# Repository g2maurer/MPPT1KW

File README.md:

# MPPT1KW
 Solar Battery Charger
   1. 4/18/2023 Added PCB files (KiCad).
   2. 10/11/2023 Updated BOM files:
      MPPT_1KW_ESP32_ggmV3.xlsx
      MPPT V3 BOM.pdf
   4. 04/23/2024 Added new enclosure design (new design was done with FreeCAD).
      The dimensions have not changed but the new design incorporates the fan and vent grills.

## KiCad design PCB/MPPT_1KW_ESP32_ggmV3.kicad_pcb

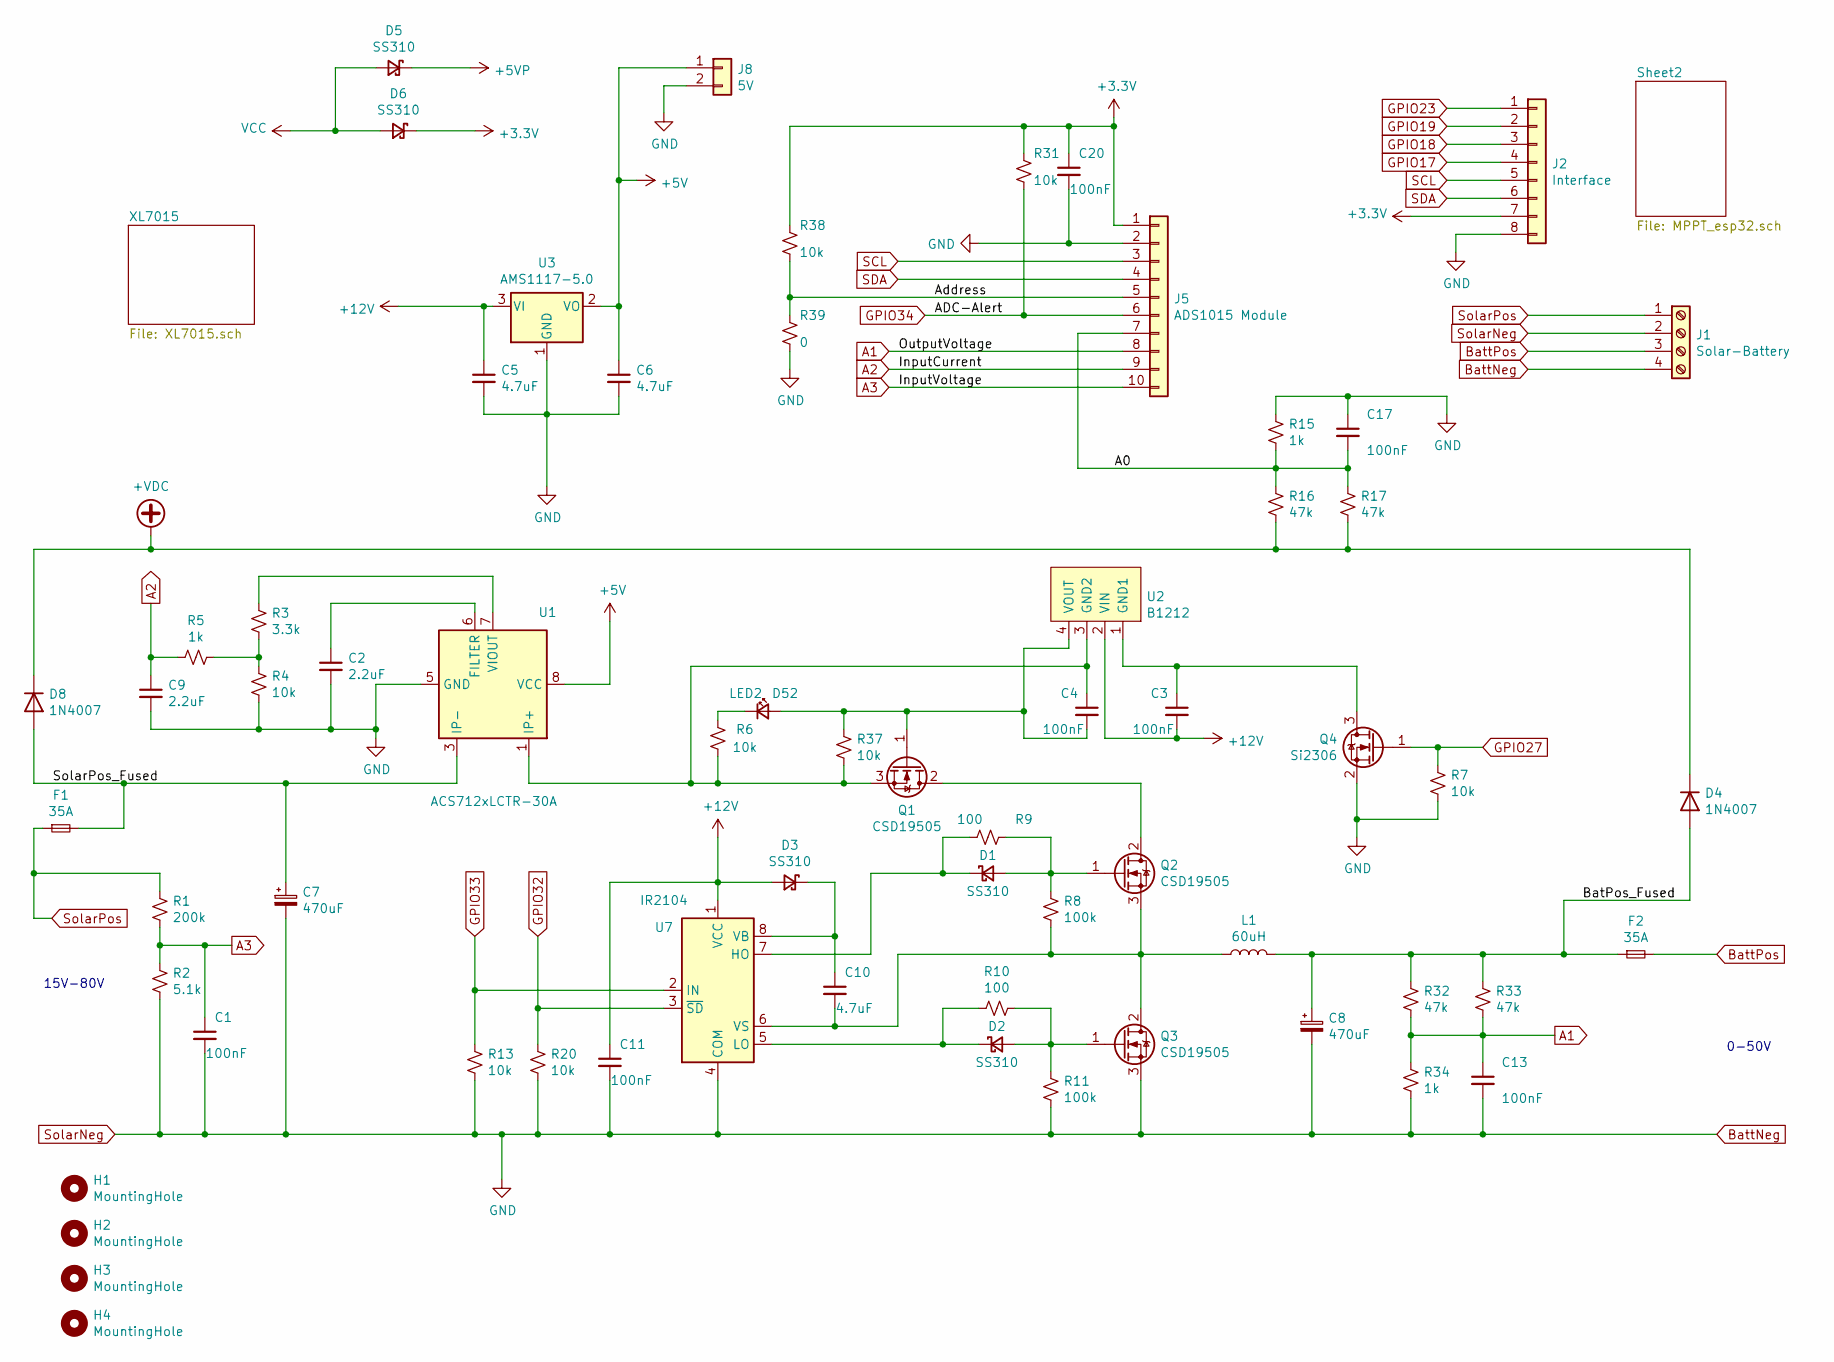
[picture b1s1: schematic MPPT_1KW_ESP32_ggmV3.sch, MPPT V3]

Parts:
C1, C3, C4, C11, C13, C17, C20: 100nF; C_0805_2012Metric_Pad1.18x1.45mm_HandSolder
C2, C9: 2.2uF; C_0805_2012Metric_Pad1.18x1.45mm_HandSolder
C5, C6, C10: 4.7uF; C_1206_3216Metric_Pad1.33x1.80mm_HandSolder
C7, C8: 470uF; CP_Radial_D16.0mm_P7.50mm
D1, D2, D3, D5, D6: SS310; D_2010_5025Metric_Pad1.52x2.65mm_HandSolder
D4, D8: 1N4007; D_2010_5025Metric_Pad1.52x2.65mm_HandSolder
D52: LED2; LED_0805_2012Metric_Pad1.15x1.40mm_HandSolder
F1, F2: 35A; Mini_Blade
H1, H2, H3, H4: MountingHole; MountingHole_2.7mm
J1: Solar-Battery; Conn-Screw-4-term
J2: Interface; JST_XH_B8B-XH-A_1x08_P2.50mm_Vertical
J5: ADS1015 Module; JST_XH_B10B-XH-A_1x10_P2.50mm_Vertical
J8: 5V; JST_XH_B2B-XH-A_1x02_P2.50mm_Vertical
L1: 60uH; L_Toroid_Vertical_L41.9mm_W17.8mm_P12.70mm_Pulse_F
Q1, Q2, Q3: CSD19505; TO-220-3_Vertical
Q4: Si2306; SOT-23
R1: 200k; R_0805_2012Metric_Pad1.20x1.40mm_HandSolder
R2: 5.1k; R_0805_2012Metric_Pad1.20x1.40mm_HandSolder
R3: 3.3k; R_0805_2012Metric_Pad1.20x1.40mm_HandSolder
R4, R6, R7, R13, R20, R31, R37, R38: 10k; R_0805_2012Metric_Pad1.20x1.40mm_HandSolder
R5, R15, R34: 1k; R_0805_2012Metric_Pad1.20x1.40mm_HandSolder
R8, R11: 100k; R_0805_2012Metric_Pad1.20x1.40mm_HandSolder
R9, R10: 100; R_0805_2012Metric_Pad1.20x1.40mm_HandSolder
R16, R17, R32, R33: 47k; R_0805_2012Metric_Pad1.20x1.40mm_HandSolder
R39: 0; R_0805_2012Metric_Pad1.20x1.40mm_HandSolder
U1: ACS712xLCTR-30A; SOIC-8_3.9x4.9mm_P1.27mm
U2: B1212; B1212S
U3: AMS1117-5.0; SOT-223-3_TabPin2
U7: IR2104; SOIC-8_3.9x4.9mm_P1.27mm

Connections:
+3V3: C20.1, D6.1 (K), J2.7, J5.1, R31.1, R38.1; also elsewhere on the board
+5V: C6.1, J8.1, U1.8 (VCC), U3.2 (VO)
+5VP: D5.1 (K); also elsewhere on the board
+12V: C3.2, C5.1, C11.1, D3.2 (A), U2.2 (VIN), U3.3 (VI), U7.1 (VCC); also elsewhere on the board
+VDC: D4.1 (K), D8.1 (K), R16.2, R17.2; also elsewhere on the board
/A0: C17.2, J5.7, R15.2, R16.1, R17.1
/Address: J5.5, R38.2, R39.1
/BatPos_Fused: C8.1, D4.2 (A), F2.1, L1.2, R32.1, R33.1
/SolarPos_Fused: C7.1, D8.2 (A), F1.2, U1.3 (IP-), U1.4 (IP-)
A1: C13.1, J5.8, R32.2, R33.2, R34.1
A2: C9.1, J5.9, R5.2
A3: C1.1, J5.10, R1.2, R2.1
BattNeg: C1.2, C2.2, C5.2, C6.2, C7.2, C8.2, C9.2, C11.2, C13.2, C17.1, C20.2, J1.2, J1.4, J2.8, J5.2, J8.2, Q3.3 (S), Q4.2 (S), R2.2, R4.2, R7.2, R11.2, R13.2, R15.1, R20.2, R34.2, R39.2, U1.5 (GND), U3.1 (GND), U7.4 (COM); also elsewhere on the board
BattPos: F2.2, J1.3
GPIO17: J2.4; also elsewhere on the board
GPIO18: J2.3; also elsewhere on the board
GPIO19: J2.2; also elsewhere on the board
GPIO23: J2.1; also elsewhere on the board
GPIO27: Q4.1 (G), R7.1; also elsewhere on the board
GPIO32: R20.1, U7.3 (~SD); also elsewhere on the board
GPIO33: R13.1, U7.2 (IN); also elsewhere on the board
GPIO34: J5.6, R31.2; also elsewhere on the board
unnamed: C2.1, U1.6 (FILTER)
unnamed: C3.1, Q4.3 (D), U2.1 (GND1)
unnamed: C4.1, Q1.3 (S), R6.1, R37.2, U1.1 (IP+), U1.2 (IP+), U2.3 (GND2)
unnamed: C4.2, D52.2 (A), Q1.1 (G), R37.1, U2.4 (VOUT)
unnamed: C10.1, D3.1 (K), U7.8 (VB)
unnamed: C10.2, L1.1, Q2.3 (S), Q3.2 (D), R8.2, U7.6 (VS)
unnamed: D1.1 (K), R9.2, U7.7 (HO)
unnamed: D1.2 (A), Q2.1 (G), R8.1, R9.1
unnamed: D2.1 (K), R10.2, U7.5 (LO)
unnamed: D2.2 (A), Q3.1 (G), R10.1, R11.1
unnamed: D52.1 (K), R6.2
unnamed: Q1.2 (D), Q2.2 (D)
unnamed: R3.1, U1.7 (VIOUT)
unnamed: R3.2, R4.1, R5.1
SCL: J2.5, J5.3; also elsewhere on the board
SDA: J2.6, J5.4; also elsewhere on the board
SolarPos: F1.1, J1.1, R1.1
VCC: D5.2 (A), D6.2 (A); also elsewhere on the board

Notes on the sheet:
15V-80V
0-50V

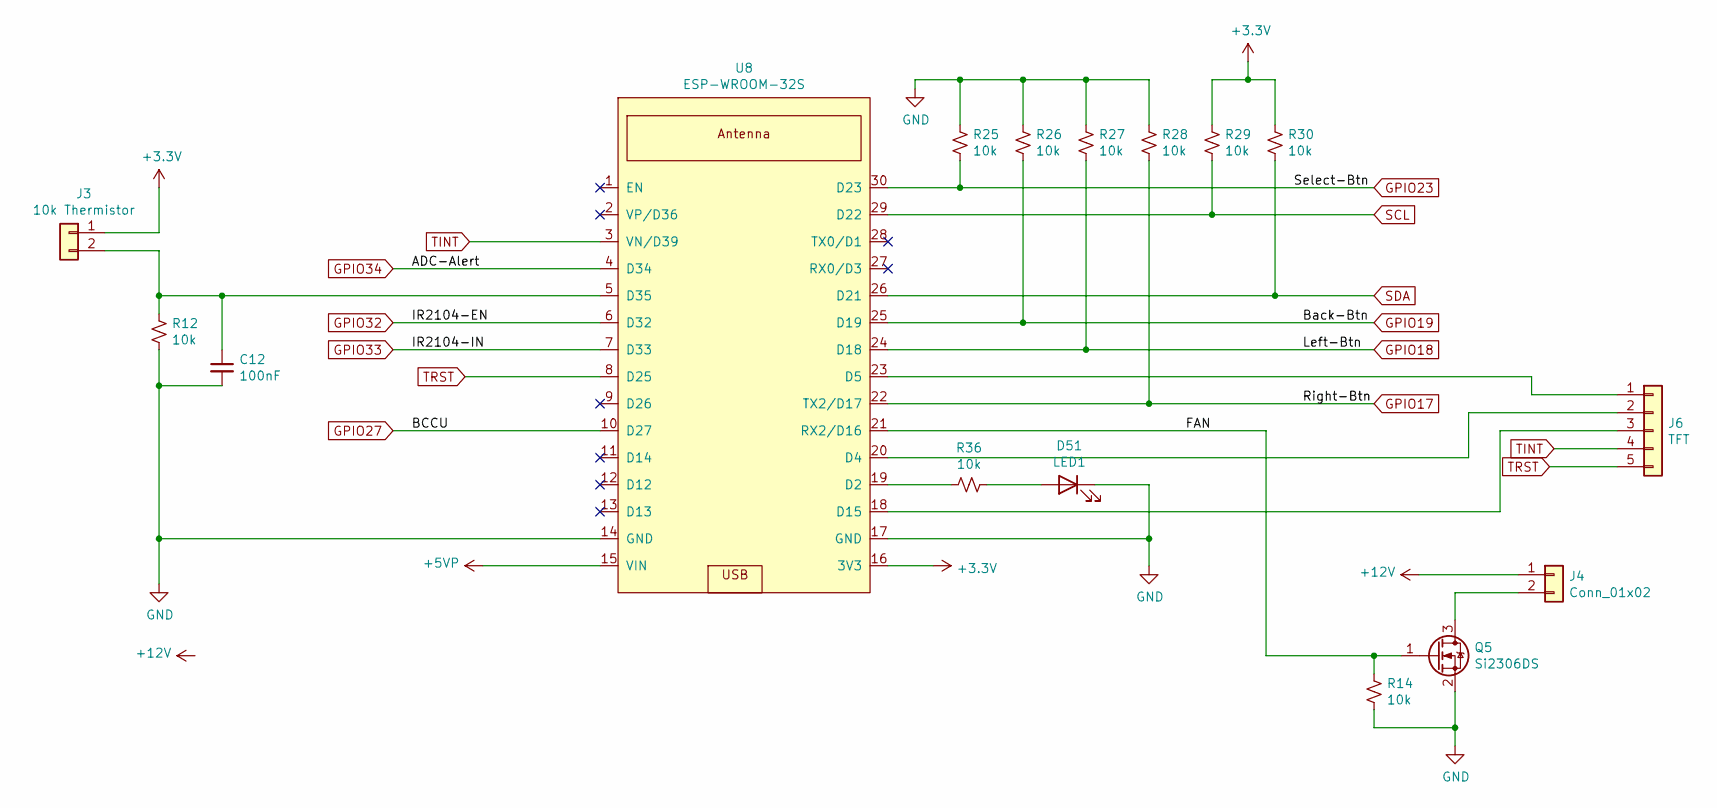
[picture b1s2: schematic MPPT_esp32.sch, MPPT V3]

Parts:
C12: 100nF; C_0805_2012Metric_Pad1.18x1.45mm_HandSolder
D51: LED1; LED_0805_2012Metric_Pad1.15x1.40mm_HandSolder
J3: 10k Thermistor; JST_XH_B2B-XH-A_1x02_P2.50mm_Vertical
J4: Conn_01x02; JST_XH_B2B-XH-A_1x02_P2.50mm_Vertical
J6: TFT; JST_XH_B5B-XH-A_1x05_P2.50mm_Vertical
Q5: Si2306DS; SOT-23
R12, R14, R25, R26, R27, R28, R29, R30, R36: 10k; R_0805_2012Metric_Pad1.20x1.40mm_HandSolder
U8: ESP-WROOM-32S

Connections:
+3V3: J3.1, R29.1, R30.1, U8.16 (3V3); also elsewhere on the board
+5VP: U8.15 (VIN); also elsewhere on the board
+12V: J4.1; also elsewhere on the board
/Sheet2/FAN: Q5.1 (G), R14.1, U8.21 (RX2/D16)
BattNeg: C12.2, D51.1 (K), Q5.2 (S), R12.2, R14.2, R25.1, R26.1, R27.1, R28.1, U8.14 (GND), U8.17 (GND); also elsewhere on the board
GPIO17: R28.2, U8.22 (TX2/D17); also elsewhere on the board
GPIO18: R27.2, U8.24 (D18); also elsewhere on the board
GPIO19: R26.2, U8.25 (D19); also elsewhere on the board
GPIO23: R25.2, U8.30 (D23); also elsewhere on the board
GPIO27: U8.10 (D27); also elsewhere on the board
GPIO32: U8.6 (D32); also elsewhere on the board
GPIO33: U8.7 (D33); also elsewhere on the board
GPIO34: U8.4 (D34); also elsewhere on the board
unnamed: C12.1, J3.2, R12.1, U8.5 (D35)
unnamed: D51.2 (A), R36.1
unnamed: J4.2, Q5.3 (D)
unnamed: J6.1, U8.23 (D5)
unnamed: J6.2, U8.20 (D4)
unnamed: J6.3, U8.18 (D15)
unnamed: R36.2, U8.19 (D2)
SCL: R29.2, U8.29 (D22); also elsewhere on the board
SDA: R30.2, U8.26 (D21); also elsewhere on the board
TINT: J6.4, U8.3 (VN/D39)
TRST: J6.5, U8.8 (D25)

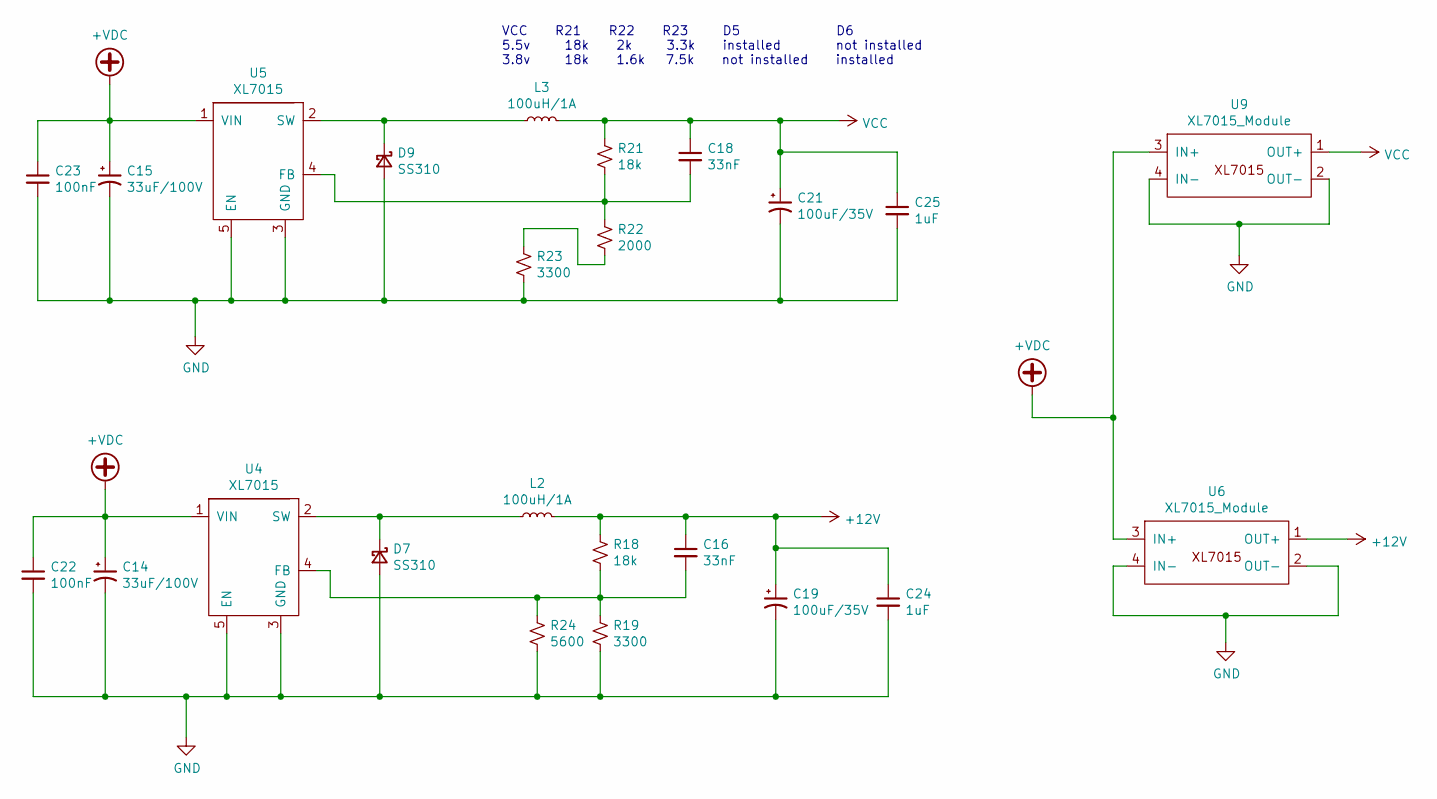
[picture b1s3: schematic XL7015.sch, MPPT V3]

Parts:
C14, C15: 33uF/100V; CP_Radial_D8.0mm_P2.50mm
C16, C18: 33nF; C_0805_2012Metric_Pad1.18x1.45mm_HandSolder
C19, C21: 100uF/35V; CP_Radial_D6.3mm_P2.50mm
C22, C23: 100nF; C_0805_2012Metric_Pad1.18x1.45mm_HandSolder
C24, C25: 1uF; C_0805_2012Metric_Pad1.18x1.45mm_HandSolder
D7, D9: SS310; D_2010_5025Metric_Pad1.52x2.65mm_HandSolder
L2, L3: 100uH/1A; L_Taiyo-Yuden_NR-60xx_HandSoldering
R18, R21: 18k; R_0805_2012Metric_Pad1.20x1.40mm_HandSolder
R19, R23: 3300; R_0805_2012Metric_Pad1.20x1.40mm_HandSolder
R22: 2000; R_0805_2012Metric_Pad1.20x1.40mm_HandSolder
R24: 5600; R_0805_2012Metric_Pad1.20x1.40mm_HandSolder
U4, U5: XL7015; TO-252-5_TabPin3
U6, U9: XL7015_Module; Module_XL7015

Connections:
+12V: C16.1, C19.1, C24.1, L2.2, R18.1, U6.1 (OUT+); also elsewhere on the board
+VDC: C14.1, C15.1, C22.1, C23.1, U4.1 (VIN), U5.1 (VIN), U6.3 (IN+), U9.3 (IN+); also elsewhere on the board
BattNeg: C14.2, C15.2, C19.2, C21.2, C22.2, C23.2, C24.2, C25.2, D7.2 (A), D9.2 (A), R19.2, R23.2, R24.2, U4.3 (GND), U4.5 (EN), U5.3 (GND), U5.5 (EN), U6.2 (OUT-), U6.4 (IN-), U9.2 (OUT-), U9.4 (IN-); also elsewhere on the board
unnamed: C16.2, R18.2, R19.1, R24.1, U4.4 (FB)
unnamed: C18.2, R21.2, R22.1, U5.4 (FB)
unnamed: D7.1 (K), L2.1, U4.2 (SW)
unnamed: D9.1 (K), L3.1, U5.2 (SW)
unnamed: R22.2, R23.1
VCC: C18.1, C21.1, C25.1, L3.2, R21.1, U9.1 (OUT+); also elsewhere on the board

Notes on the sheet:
VCC R21 R22 R23 D5 D6 5.5v 18k 2k 3.3k installed not installed 3.8v 18k 1.6k 7.5k not installed installed

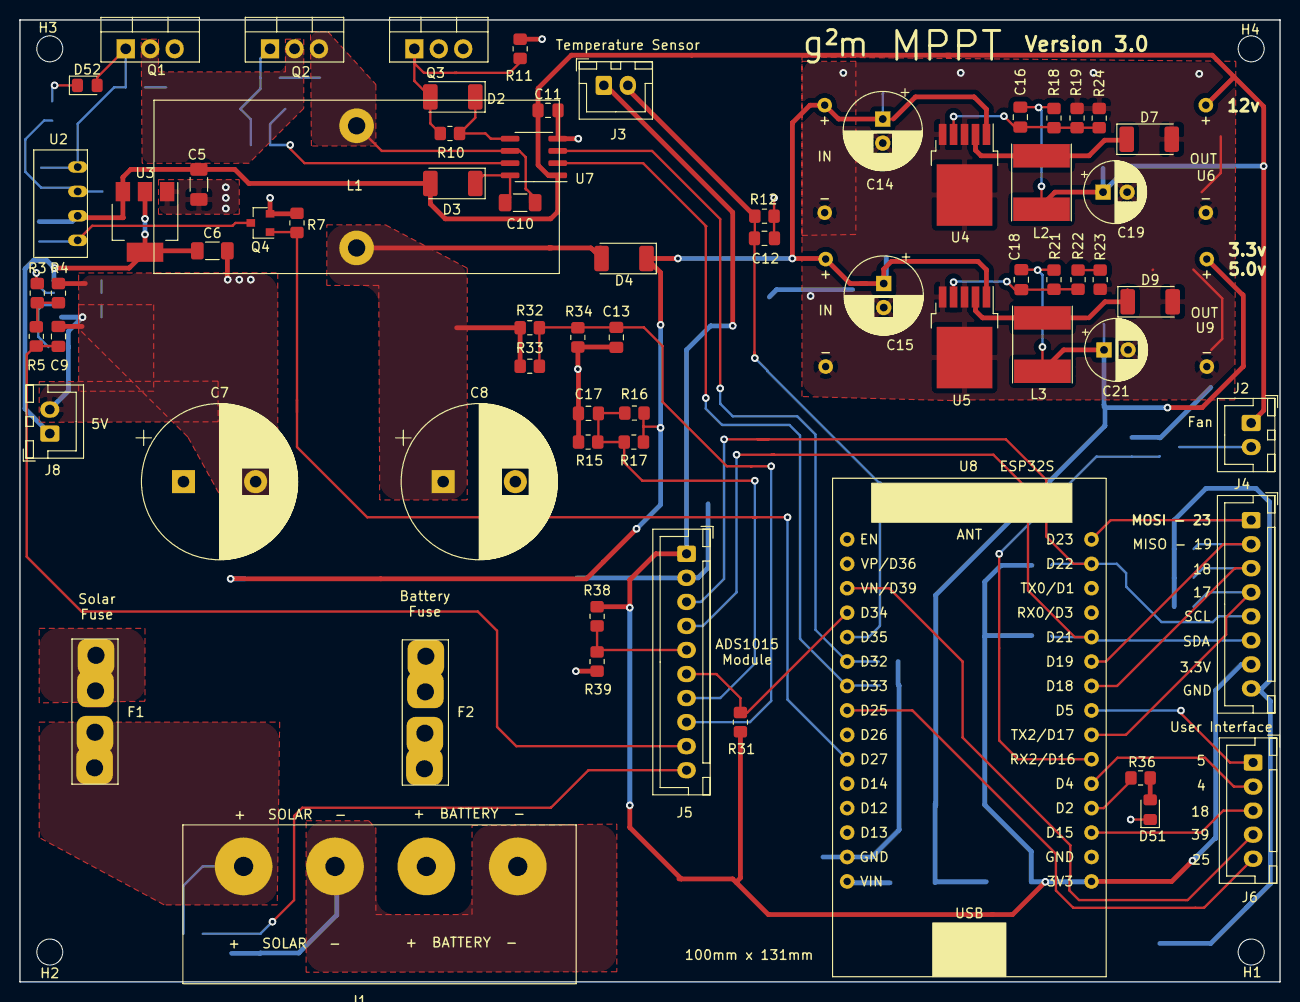
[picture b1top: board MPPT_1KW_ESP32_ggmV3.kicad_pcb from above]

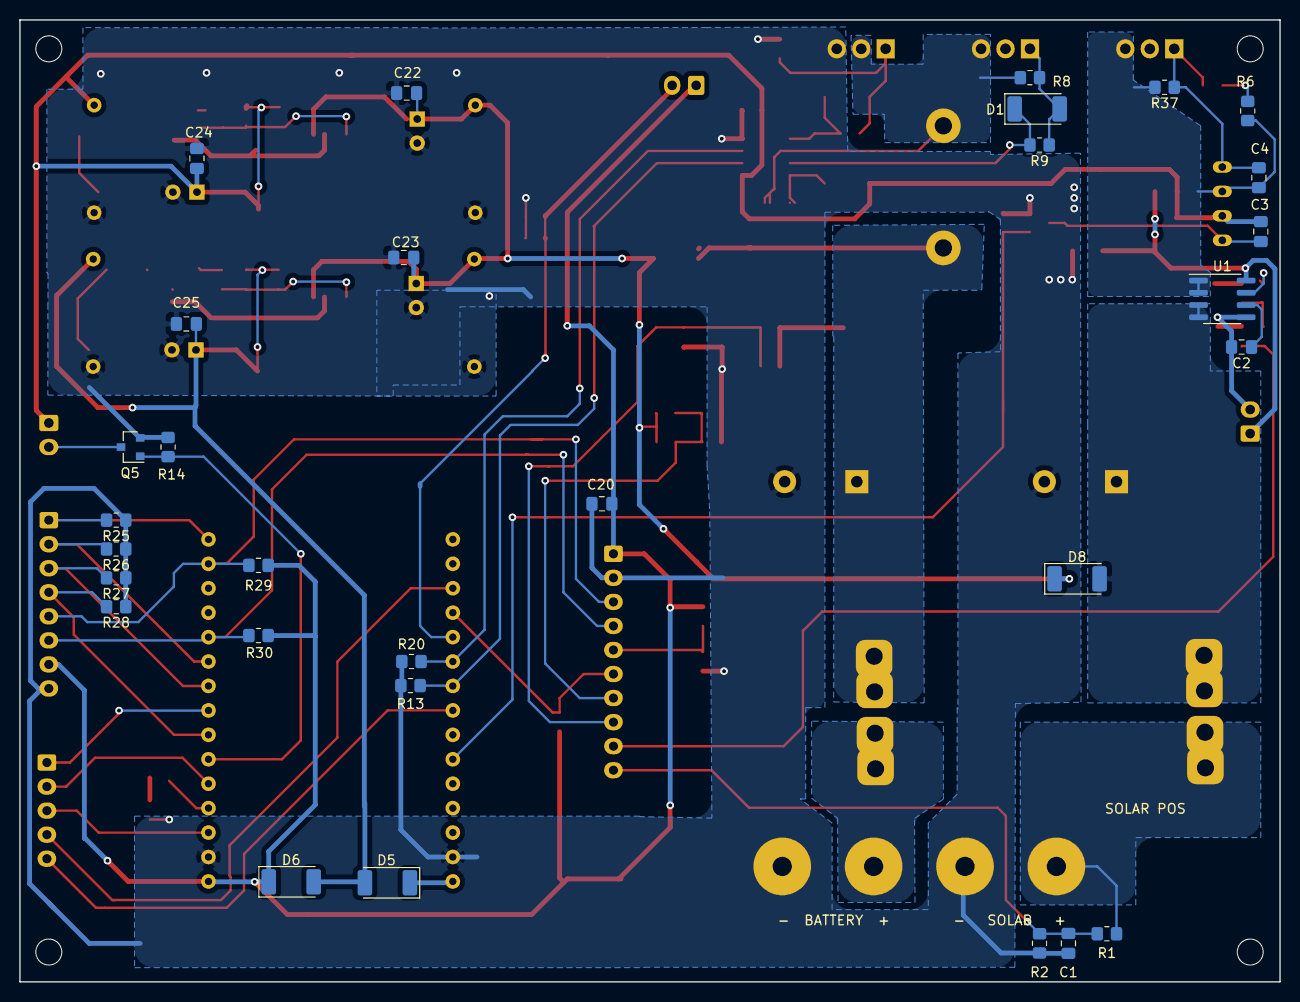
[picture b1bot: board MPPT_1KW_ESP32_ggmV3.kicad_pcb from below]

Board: 2 copper layers, 131.0 x 100.0 mm, 104 parts (30 on the bottom side), 55 nets.

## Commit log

2023-04-18 Initial post
2023-04-18 Move to PCB folder
2023-10-11 Updated BOM
2024-04-18 Added STL files to project.
    TinkerCAD STL files for enclosure.
2024-04-23 Add new enclosure design
    Redesigned MPPT enclosure using FreeCAD.
2024-04-23 Replaced Enclosure STL File
2024-04-24 Update STLs
    Update the STL generated from FreeCAD.
